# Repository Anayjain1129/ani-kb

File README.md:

# Ani-keeb

### Why did I make it?
It was a project of blueprint but i just never completed it. and like i almost went offline from hackclub then i heard about Reboot. that's why i built it and completed it.

Features:

- Raspberry Pi Pico
- Customised layout
- QMK firmware
- cool silkscreen
- Custom case

### Schematic

### PCB 

### Case

### 3D view of all parts together

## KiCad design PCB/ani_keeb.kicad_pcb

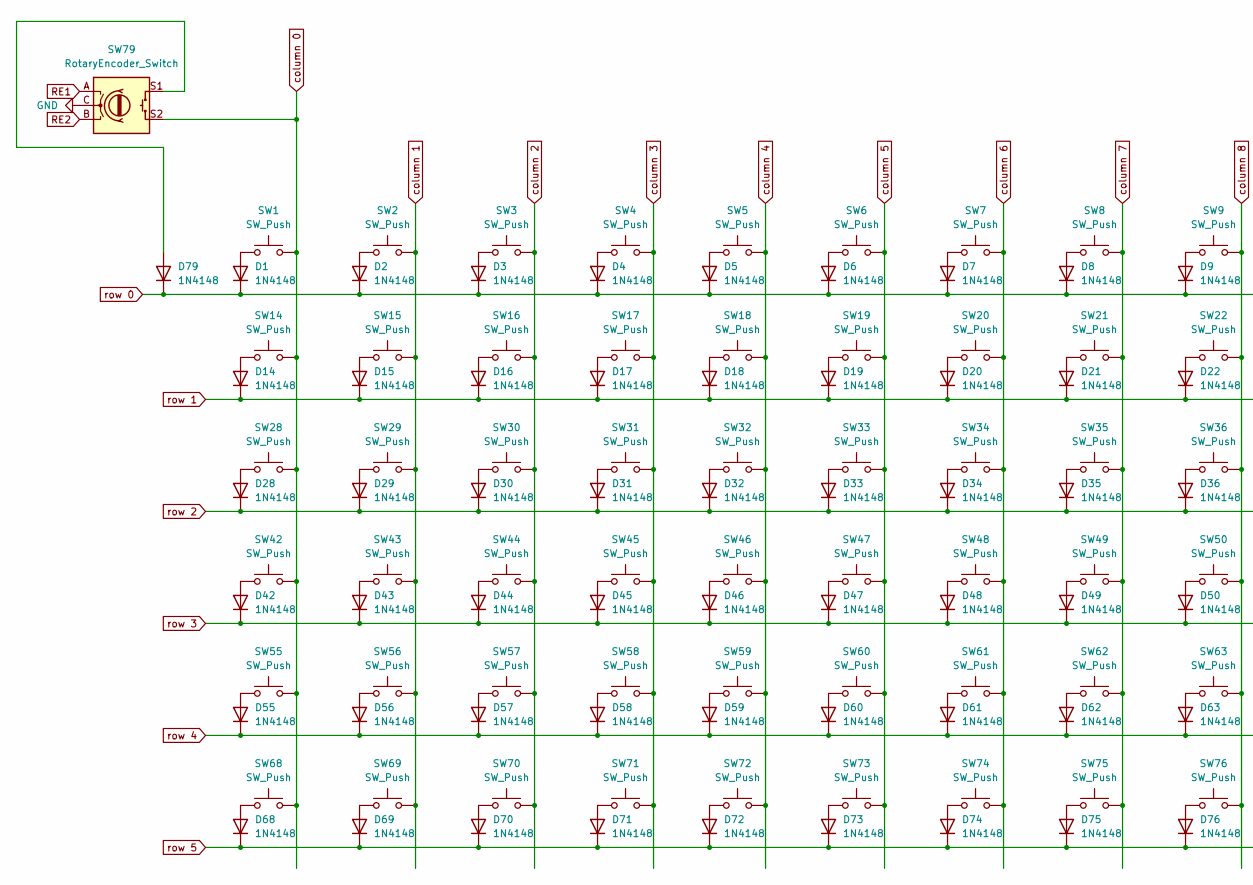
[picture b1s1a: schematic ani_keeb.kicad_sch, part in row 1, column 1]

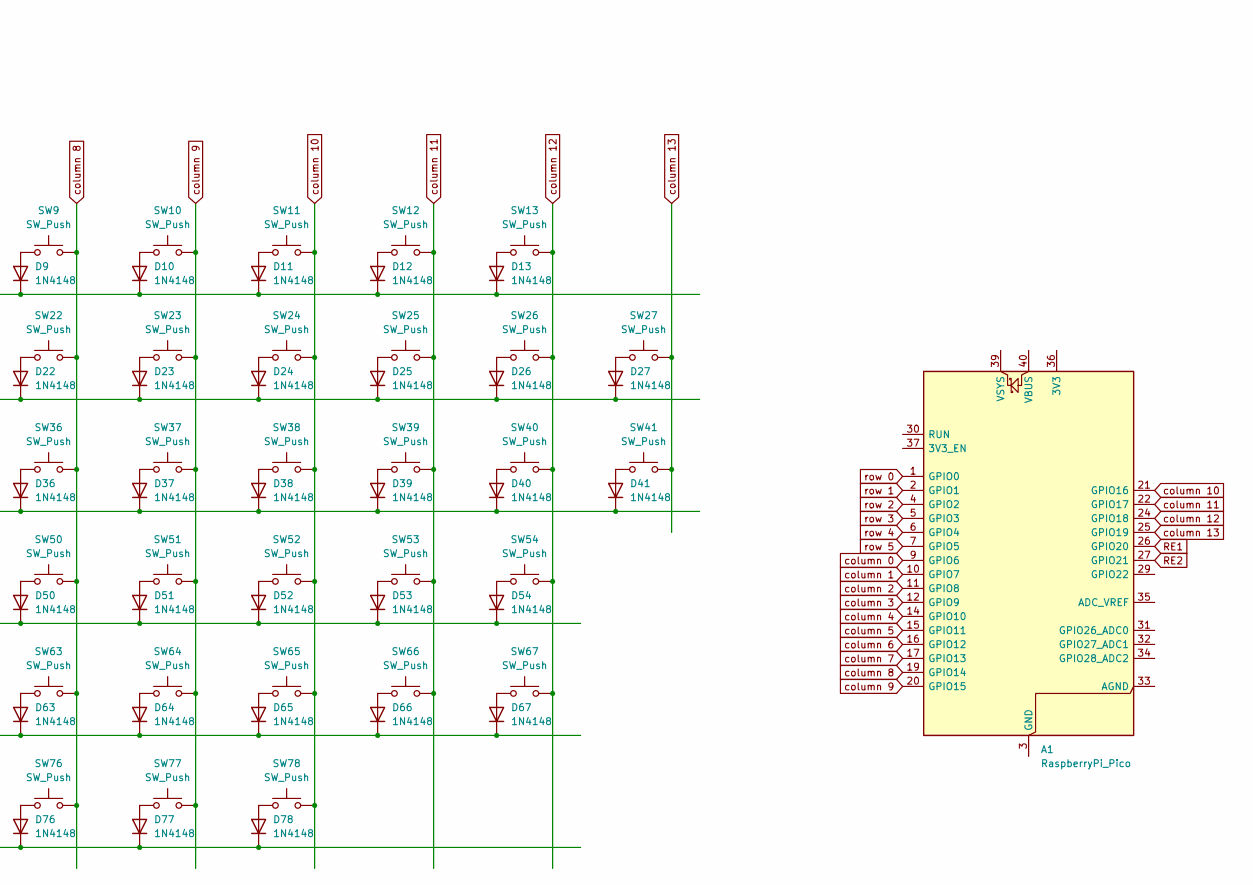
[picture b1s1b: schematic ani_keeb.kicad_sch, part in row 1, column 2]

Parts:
A1: RaspberryPi_Pico; RaspberryPi_Pico_Common_Unspecified
D1, D2, D3, D4, D5, D6, D7, D8, D9, D10, D11, D12, D13, D14, D15, D16, D17, D18, D19, D20, D21, D22, D23, D24, D25, D26, D27, D28, D29, D30, D31, D32, D33, D34, D35, D36, D37, D38, D39, D40, D41, D42, D43, D44, D45, D46, D47, D48, D49, D50, D51, D52, D53, D54, D55, D56, D57, D58, D59, D60, D61, D62, D63, D64, D65, D66, D67, D68, D69, D70, D71, D72, D73, D74, D75, D76, D77, D78, D79: 1N4148; D_DO-35_SOD27_P7.62mm_Horizontal
SW1, SW2, SW3, SW4, SW5, SW6, SW7, SW8, SW9, SW10, SW11, SW12, SW13, SW14, SW15, SW16, SW17, SW18, SW19, SW20, SW21, SW22, SW23, SW24, SW25, SW26, SW29, SW30, SW31, SW32, SW33, SW34, SW35, SW36, SW37, SW38, SW39, SW40, SW43, SW44, SW45, SW46, SW47, SW48, SW49, SW50, SW51, SW52, SW53, SW56, SW57, SW58, SW59, SW60, SW61, SW62, SW63, SW64, SW65, SW67, SW76, SW77, SW78: SW_Push; SW_Cherry_MX_1.00u_PCB
SW27: SW_Push; SW_Cherry_MX_2.00u_PCB
SW28, SW41: SW_Push; SW_Cherry_MX_1.50u_PCB
SW42: SW_Push; SW_Cherry_MX_1.75u_PCB
SW54, SW55: SW_Push; SW_Cherry_MX_2.25u_PCB
SW66: SW_Push; SW_Cherry_MX_2.75u_PCB
SW68, SW69, SW70, SW72, SW73, SW74, SW75: SW_Push; SW_Cherry_MX_1.25u_PCB
SW71: SW_Push; SW_Cherry_MX_6.25u_PCB
SW79: RotaryEncoder_Switch; RotaryEncoder_Alps_EC11E-Switch_Vertical_H20mm_CircularMoun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

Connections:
GND: SW79.C
unnamed: A1.3 (GND), A1.8 (GND), A1.13 (GND), A1.18 (GND), A1.23 (GND), A1.28 (GND), A1.38 (GND)
unnamed: D1.2 (A), SW1.1
unnamed: D2.2 (A), SW2.1
unnamed: D3.2 (A), SW3.1
unnamed: D4.2 (A), SW4.1
unnamed: D5.2 (A), SW5.1
unnamed: D6.2 (A), SW6.1
unnamed: D7.2 (A), SW7.1
unnamed: D8.2 (A), SW8.1
unnamed: D9.2 (A), SW9.1
unnamed: D10.2 (A), SW10.1
unnamed: D11.2 (A), SW11.1
unnamed: D12.2 (A), SW12.1
unnamed: D13.2 (A), SW13.1
unnamed: D14.2 (A), SW14.1
unnamed: D15.2 (A), SW15.1
unnamed: D16.2 (A), SW16.1
unnamed: D17.2 (A), SW17.1
unnamed: D18.2 (A), SW18.1
unnamed: D19.2 (A), SW19.1
unnamed: D20.2 (A), SW20.1
unnamed: D21.2 (A), SW21.1
unnamed: D22.2 (A), SW22.1
unnamed: D23.2 (A), SW23.1
unnamed: D24.2 (A), SW24.1
unnamed: D25.2 (A), SW25.1
unnamed: D26.2 (A), SW26.1
unnamed: D27.2 (A), SW27.1
unnamed: D28.2 (A), SW28.1
unnamed: D29.2 (A), SW29.1
unnamed: D30.2 (A), SW30.1
unnamed: D31.2 (A), SW31.1
unnamed: D32.2 (A), SW32.1
unnamed: D33.2 (A), SW33.1
unnamed: D34.2 (A), SW34.1
unnamed: D35.2 (A), SW35.1
unnamed: D36.2 (A), SW36.1
unnamed: D37.2 (A), SW37.1
unnamed: D38.2 (A), SW38.1
unnamed: D39.2 (A), SW39.1
unnamed: D40.2 (A), SW40.1
unnamed: D41.2 (A), SW41.1
unnamed: D42.2 (A), SW42.1
unnamed: D43.2 (A), SW43.1
unnamed: D44.2 (A), SW44.1
unnamed: D45.2 (A), SW45.1
unnamed: D46.2 (A), SW46.1
unnamed: D47.2 (A), SW47.1
unnamed: D48.2 (A), SW48.1
unnamed: D49.2 (A), SW49.1
unnamed: D50.2 (A), SW50.1
unnamed: D51.2 (A), SW51.1
unnamed: D52.2 (A), SW52.1
unnamed: D53.2 (A), SW53.1
unnamed: D54.2 (A), SW54.1
unnamed: D55.2 (A), SW55.1
unnamed: D56.2 (A), SW56.1
unnamed: D57.2 (A), SW57.1
unnamed: D58.2 (A), SW58.1
unnamed: D59.2 (A), SW59.1
unnamed: D60.2 (A), SW60.1
unnamed: D61.2 (A), SW61.1
unnamed: D62.2 (A), SW62.1
unnamed: D63.2 (A), SW63.1
unnamed: D64.2 (A), SW64.1
unnamed: D65.2 (A), SW65.1
unnamed: D66.2 (A), SW66.1
unnamed: D67.2 (A), SW67.1
unnamed: D68.2 (A), SW68.1
unnamed: D69.2 (A), SW69.1
unnamed: D70.2 (A), SW70.1
unnamed: D71.2 (A), SW71.1
unnamed: D72.2 (A), SW72.1
unnamed: D73.2 (A), SW73.1
unnamed: D74.2 (A), SW74.1
unnamed: D75.2 (A), SW75.1
unnamed: D76.2 (A), SW76.1
unnamed: D77.2 (A), SW77.1
unnamed: D78.2 (A), SW78.1
unnamed: D79.2 (A), SW79.S1
RE1: A1.26 (GPIO20), SW79.A
RE2: A1.27 (GPIO21), SW79.B
column 0: A1.9 (GPIO6), SW1.2, SW14.2, SW28.2, SW42.2, SW55.2, SW68.2, SW79.S2
column 1: A1.10 (GPIO7), SW2.2, SW15.2, SW29.2, SW43.2, SW56.2, SW69.2
column 2: A1.11 (GPIO8), SW3.2, SW16.2, SW30.2, SW44.2, SW57.2, SW70.2
column 3: A1.12 (GPIO9), SW4.2, SW17.2, SW31.2, SW45.2, SW58.2, SW71.2
column 4: A1.14 (GPIO10), SW5.2, SW18.2, SW32.2, SW46.2, SW59.2, SW72.2
column 5: A1.15 (GPIO11), SW6.2, SW19.2, SW33.2, SW47.2, SW60.2, SW73.2
column 6: A1.16 (GPIO12), SW7.2, SW20.2, SW34.2, SW48.2, SW61.2, SW74.2
column 7: A1.17 (GPIO13), SW8.2, SW21.2, SW35.2, SW49.2, SW62.2, SW75.2
column 8: A1.19 (GPIO14), SW9.2, SW22.2, SW36.2, SW50.2, SW63.2, SW76.2
column 9: A1.20 (GPIO15), SW10.2, SW23.2, SW37.2, SW51.2, SW64.2, SW77.2
column 10: A1.21 (GPIO16), SW11.2, SW24.2, SW38.2, SW52.2, SW65.2, SW78.2
column 11: A1.22 (GPIO17), SW12.2, SW25.2, SW39.2, SW53.2, SW66.2
column 12: A1.24 (GPIO18), SW13.2, SW26.2, SW40.2, SW54.2, SW67.2
column 13: A1.25 (GPIO19), SW27.2, SW41.2
row 0: A1.1 (GPIO0), D1.1 (K), D2.1 (K), D3.1 (K), D4.1 (K), D5.1 (K), D6.1 (K), D7.1 (K), D8.1 (K), D9.1 (K), D10.1 (K), D11.1 (K), D12.1 (K), D13.1 (K), D79.1 (K)
row 1: A1.2 (GPIO1), D14.1 (K), D15.1 (K), D16.1 (K), D17.1 (K), D18.1 (K), D19.1 (K), D20.1 (K), D21.1 (K), D22.1 (K), D23.1 (K), D24.1 (K), D25.1 (K), D26.1 (K), D27.1 (K)
row 2: A1.4 (GPIO2), D28.1 (K), D29.1 (K), D30.1 (K), D31.1 (K), D32.1 (K), D33.1 (K), D34.1 (K), D35.1 (K), D36.1 (K), D37.1 (K), D38.1 (K), D39.1 (K), D40.1 (K), D41.1 (K)
row 3: A1.5 (GPIO3), D42.1 (K), D43.1 (K), D44.1 (K), D45.1 (K), D46.1 (K), D47.1 (K), D48.1 (K), D49.1 (K), D50.1 (K), D51.1 (K), D52.1 (K), D53.1 (K), D54.1 (K)
row 4: A1.6 (GPIO4), D55.1 (K), D56.1 (K), D57.1 (K), D58.1 (K), D59.1 (K), D60.1 (K), D61.1 (K), D62.1 (K), D63.1 (K), D64.1 (K), D65.1 (K), D66.1 (K), D67.1 (K)
row 5: A1.7 (GPIO5), D68.1 (K), D69.1 (K), D70.1 (K), D71.1 (K), D72.1 (K), D73.1 (K), D74.1 (K), D75.1 (K), D76.1 (K), D77.1 (K), D78.1 (K)

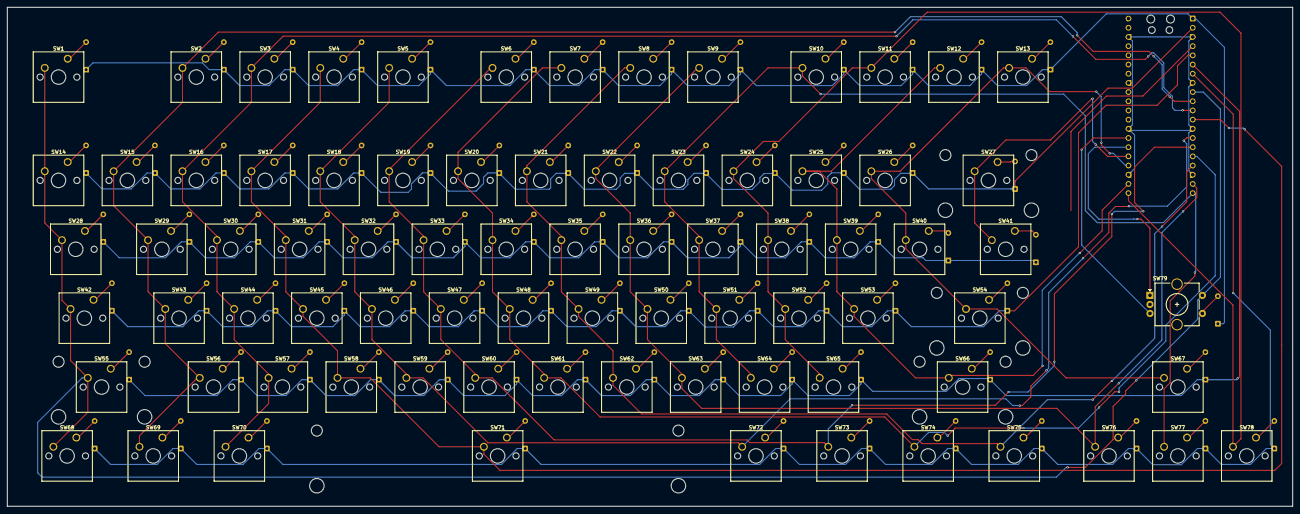
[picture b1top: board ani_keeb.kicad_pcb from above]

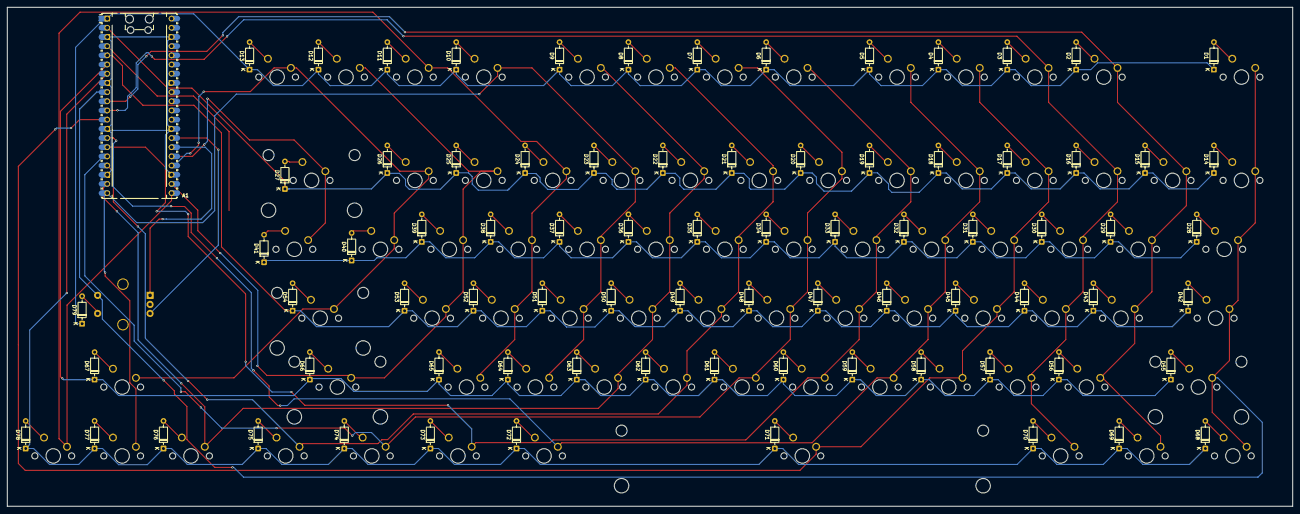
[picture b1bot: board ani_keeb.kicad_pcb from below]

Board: 2 copper layers, 355.5 x 138.0 mm, 159 parts (80 on the bottom side), 102 nets.
